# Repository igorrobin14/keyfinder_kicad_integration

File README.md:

# Séance 7 de Design : intégration sur KiCad 7.0 d'un nouveau capteur sur le keyfinder de chez Action et redimensionnement

## Igor Robin - ZZ2 - F1

### Contenu du dépôt
- Les fichiers kiCad 7.0 correspondant au schématique, au circuit imprimé, ainsi qu'au projet lui-même
- Une photo du schématique montrant le branchement du nouveau composant
- Une photo de l'éditeur de PCB montrant le réagencement des composants
- Une vue 3D du PCB avec ce nouveau composant intégré
- Ce ```README.md```

###
*Utilisation : télécharger le dépôt complet, extraire l'archive .zip, mettre tous les fichiers qu'elle contient dans un dossier choisi, mettre au même niveau que le ficher projet (.kicad_pro) le dépôt complet qui se trouve à cette adresse :*
https://github.com/NordicPlayground/nrf5-eagle-reference-design
*Ouvrir le projet dans KiCad et faire en sorte que le package nRF52832 soit prit en compte*

## Introduction
Le but de cette séance de Design était de redimensionner le PCB afin qu'il corresponde à la forme modélisée sur Fusion 360, d'y intégrer un nouveau capteur et de réagencer les composants déjà présents afin de les faire rentrer sur le PCB avec sa forme et taille finale. Concernant le capteur, nous avons eu à le choisir, déterminer son utilité pour le produit, et enfin rechercher le capteur réel pour l'intégrer.

## Mise en œuvre

### Capteur choisi
Le nouveau capteur qui a été choisi pour être intégré est un capteur d'humidité et de température ENS210

### Utilité pour le produit
L'intérêt pour le keyfinder d'avoir un capteur de température et d'humidité est de pouvoir s'en servir comme thermomètre ou baromètre, ce qui permettrait d'obtenir des informations sur l'environnement situé autour de l'object auquel est rattaché le keyfinder. Bien évidemment, il y a peu de chances que l'on mette ses clés dans un environnement extrême le plus souvent, mais cela peut en revanche servir à améliorer le niveau d'information que l'on a sur la localisation du keyfinder. Si on a placé notre objet attaché au keyfinder dans un endroit chaud/froid, humide/sec, cela peut nous apporter une information supplémentaire au moment ou on arrive a côté de l'objet cherché pour le retrouver plus rapidement. Cela permet notamment de faire la distinction au niveau de la hauteur car l'application fournie avec le keyfinder ne nous renseigne pas sur celle-ci. Par exemple : nous sommes au niveau du keyfinder sur la minicarte mais celui-ci est en fait sur la terasse dehors, sur le toit, ou dans la cave. A ce moment, la mesure de température et de pression peuvent être cruciales pour s'y retrouver.

### Recherche du composant
L'empreinte du produit sur KiCad 7.0 est celle correspodant à un capteur ENS210 AMS_QFN-4-1. Lorsqu'on va sur Octopart, le composant le plus proche que l'on trouve de cette empreinte est un ENS210-LQFM de chez ScioSense.
Ses caractéristiques sont les suivantes :
- Technologie de communication utilisée : I²C
- Taille : 2.00 mm * 2.00 mm * 0.75 mm
- Prix : 1,727 $ / 100 unités achetées
- Disponibilité : disponible sur Digikey et Mouser notamment (stock de 170000 et 15000 respectivement)

### Lien pour acheter le composant
https://www.digikey.fr/en/products/detail/ENS210-LQFM/2618-ENS210-LQFMCT-ND/6490749?curr=usd&utm_campaign=buynow&utm_medium=aggregator&utm_source=octopart

### Défis relevés
- Afin de faire rentrer tous les composants sur la forme finale du PCB, le choix a été fait de retirer l'antenne Bluetooth mise au cours de la séance 5 pour la remplacer par un simple fil plus épais et mit en zig-zag
- Un défi important a été de corriger les erreurs signalées au moment de la réalisation de la DRC, mais celles-ci ont bel et bien été supprimées en routant correctement les fils pour relier les composants
- Il n'a pas fallu modifier la mécanique du PCB et/ou du keyfinder
- Une question subsiste : l'empreinte du porte-pile mit lors de la séance 6 n'est pas disponible sur KiCad 7.0 et par conséquent il n'est pas possible de savoir s'il peut être intégré sur l'autre face du PCB, néanmoins la place peut être jugée suffisamment grande, et il y a donc de grandes chances qu'il puisse être intégré.

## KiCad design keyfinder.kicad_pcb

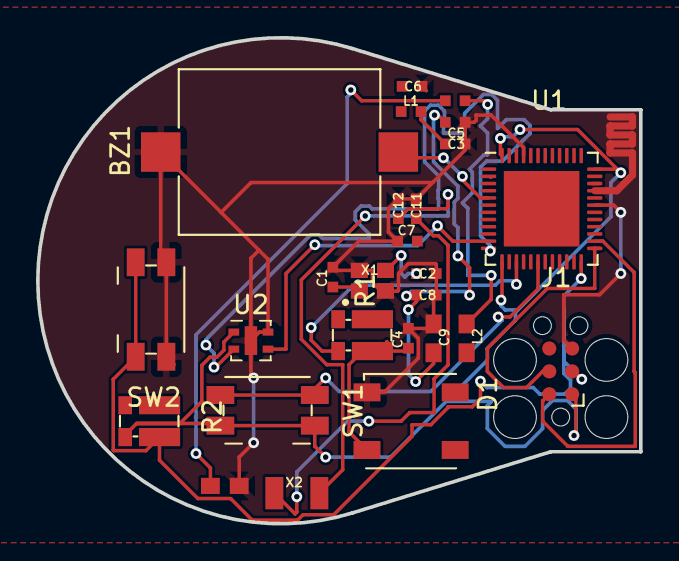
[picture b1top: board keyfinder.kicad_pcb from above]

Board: 2 copper layers, 33.5 x 27.0 mm, 26 parts (0 on the bottom side), 19 nets.

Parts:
BZ1: Buzzer; Buzzer_Mallory_AST1109MLTRQ
C1, C2, C11, C12: 12pF; RESC0402_N
C3: 0.8pF; RESC0402_N
C4, C5, C8: 100nF; RESC0402_N
C6: N.M.; RESC0402_N
C7: 100pF; RESC0402_N
C9: 4.7µF; RESC0603_N
C10: 1.0µF; RESC0603_N
D1: LED; LED_Inolux_IN-PI554FCH_PLCC4_5.0x5.0mm_P3.2mm
J1: Conn_ARM_SWD_TagConnect_TC2030; Tag-Connect_TC2030-IDC-FP_2x03_P1.27mm_Vertical
L1: 3.9nH; RESC0402_N
L2: 10µH; RESC0603_N
L3: 15nH; RESC0402_N
R1, R2: 75; R_Shunt_Vishay_WSKW0612
SW1, SW2: SW_Push; Panasonic_EVQPUJ_EVQPUA
U1: NRF52832; QFN-48-1EP_6x6mm_P0.4mm_EP4.2x4.2mm
U2: ENS210; AMS_QFN-4-1EP_2x2mm_P0.95mm_EP0.7x1.6mm
X1: 32MHz; BT-XTAL_2016_N
X2: 32.768kHz; XTAL_3215_N

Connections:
/P0.03: BZ1.1 (-), U1.5 (P0.03/AIN1@05)
/P0.09: U1.11 (P0.09/NFC1@11), U2.3 (SDA)
/P0.10: C10.1, L3.2
/P0.12: R1.2, U1.15 (P0.12@15)
/P0.15: SW1.2, U1.18 (P0.15@18)
/SWDCLK: J1.4 (SWCLK), U1.25 (SWDCLK@25)
/SWDIO: J1.2 (SWDIO), U1.26 (SWDIO@26)
ANT: C1.1, X1.1
DEC2: C2.1, X1.3
DEC3: C3.1, L1.1
GND: BZ1.2 (+), C1.2, C2.2, C3.2, C4.2, C5.2, C6.2, C7.2, C8.2, C9.2, C10.2, C11.1, C12.1, D1.1 (K), J1.5 (GND), SW2.2, U1.31 (VSS@31), U1.45 (VSS@45), U2.4 (GND), U2.5 (GND), X1.2, X1.4
unnamed: C4.1, D1.2 (A), R1.1
unnamed: J1.3 (~RESET), R2.1, SW2.1, U1.24 (P0.21/RESET@24)
unnamed: U1.12 (P0.10/NFC2@12), U2.2 (SCL)
P0.10: L2.2, L3.1
P0.20: C11.2, X2.1
P0.21/RESET: C12.2, X2.2
SWDCLK: C5.1, C8.1, C9.1
VCC: J1.1 (VCC), R2.2, SW1.1, U1.13 (VDD@13), U1.36 (VDD@36), U1.48 (VDD@48), U2.1 (VDD)

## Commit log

2023-12-09 Premier commit séance 7
    Ajout du README.md, des photos et des fichiers du projet
